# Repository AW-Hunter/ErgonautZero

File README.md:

# Ergonaut Zero

*Ergonaut Zero in Modern Case*

Ergonaut Zero is fork for an open-source ergonomic wireless split mechanical keyboard Ergonaut Zero designed by Ergonaut Keyboards.
It's based on RP2040 Zero MCU and use wire between split, unlike original.

## Features

* Low-profile, which will reduce strain on your beautiful hands;
* Split. You can put the keyboard where it'll be comfortable exactly for you;
* Wide availability and range of [compatible keycaps](https://ergonautkb.com/docs/switches/gateron-low-profile#keycaps-compatibility);
* Easily replaceable [switches](https://ergonautkb.com/docs/switches/gateron-low-profile#ks-33-v2) thanks to hot-swap sockets;
* Budget-friendly, because:
  * It uses relatively cheap and widely available RP2040 Zero as MCU;
  * It uses one PCB design for both halves of the keyboard;
  * Everything except PCB's, components and hardware (screws, nuts) can be 3D printed.
* Beginner-friendly, because:
  * PCB is easy to solder;
  * Cases are easy to print.
* Free in terms of hardware design. It's licensed under permissive [CERN-OHL-P v2](https://ohwr.org/cern_ohl_p_v2.pdf) license, which means:
  * you are free to manufacture it yourself;
  * you are free to sell your manufactured hardware for profit.

## Build Guide

In progress

## Firmware

Firmware can be found in this repository.

## Gerbers

REPLACE!!

| Front                                            | Back                                                 |
| ------------------------------------------------ | ---------------------------------------------------- |
|  |  |

* [Gerbers for JLCPCB](../../releases/latest/download/pcb-JLCPCB_gerbers.zip)
* [Gerbers for PCBWay](../../releases/latest/download/pcb-PCBWay_gerbers.zip)

## Contacts

* Documentation portal of original board: https://ergonautkb.com
* Telegram of original board: https://ergonautkb.t.me
* Telegram of original board (ru): https://ergonautkb_ru.t.me
*

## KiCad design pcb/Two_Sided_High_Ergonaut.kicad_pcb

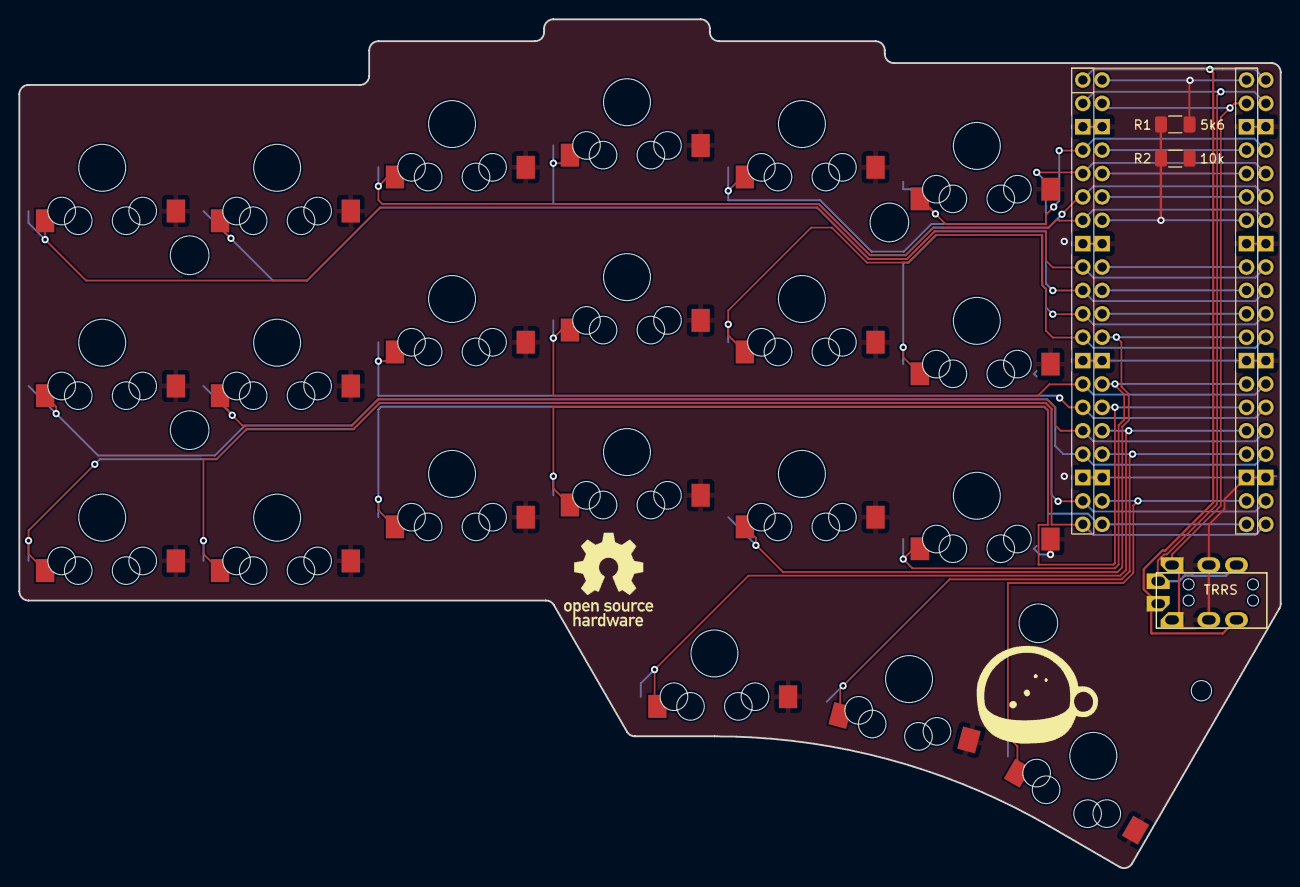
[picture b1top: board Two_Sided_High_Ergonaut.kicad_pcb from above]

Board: 2 copper layers, 137.0 x 92.2 mm, 30 parts (0 on the bottom side), 27 nets.

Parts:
H1, H2, H3, H4: MountingHole; Hole_4.2mm
H8: StandoffHole; Hole_2.2mm
J1: TRRS; MJ-4PP-9_Cantor_MX_TX-RX_Crossover
R1: 5k6; R_1206_3216Metric_Pad1.30x1.75mm_HandSolder
R2: 10k; R_1206_3216Metric_Pad1.30x1.75mm_HandSolder
SW1, SW2, SW3, SW4, SW5, SW6, SW7, SW8, SW9, SW10, SW11, SW12, SW13, SW14, SW15, SW16, SW17, SW18, SW19, SW20, SW21: SW_SPST; KS-27_KS-33_Hotswap_1U_DUAL
U2: Pico; RPi_Pico_SMD_TH

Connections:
GND: J1.3 (RING1), J1.4 (RING2), R2.2, SW1.2 (B), SW2.2 (B), SW3.2 (B), SW4.2 (B), SW5.2 (B), SW6.2 (B), SW7.2 (B), SW8.2 (B), SW9.2 (B), SW10.2 (B), SW11.2 (B), SW12.2 (B), SW13.2 (B), SW14.2 (B), SW15.2 (B), SW16.2 (B), SW17.2 (B), SW18.2 (B), SW19.2 (B), SW20.2 (B), SW21.2 (B), U2.3 (GND), U2.8 (GND), U2.13 (GND), U2.18 (GND), U2.23 (GND), U2.28 (GND), U2.33 (AGND), U2.38 (GND)
unnamed: SW1.1 (A), U2.9 (GPIO6)
unnamed: SW2.1 (A), U2.10 (GPIO7)
unnamed: SW3.1 (A), U2.7 (GPIO5)
unnamed: SW4.1 (A), U2.6 (GPIO4)
unnamed: SW5.1 (A), U2.5 (GPIO3)
unnamed: SW6.1 (A), U2.4 (GPIO2)
unnamed: SW7.1 (A), U2.17 (GPIO13)
unnamed: SW8.1 (A), U2.16 (GPIO12)
unnamed: SW9.1 (A), U2.15 (GPIO11)
unnamed: SW10.1 (A), U2.14 (GPIO10)
unnamed: SW11.1 (A), U2.12 (GPIO9)
unnamed: SW12.1 (A), U2.11 (GPIO8)
unnamed: SW13.1 (A), U2.19 (GPIO14)
unnamed: SW16.1 (A), U2.26 (GPIO20)
unnamed: SW15.1 (A), U2.21 (GPIO16)
unnamed: SW14.1 (A), U2.20 (GPIO15)
unnamed: SW17.1 (A), U2.29 (GPIO22)
unnamed: SW18.1 (A), U2.27 (GPIO21)
unnamed: SW19.1 (A), U2.25 (GPIO19)
unnamed: SW20.1 (A), U2.24 (GPIO18)
unnamed: SW21.1 (A), U2.22 (GPIO17)
RX: J1.1 (SLEEVE), J1.4 (RING2), U2.2 (GPIO1)
TX: J1.1 (SLEEVE), J1.3 (RING1), U2.1 (GPIO0)
VBUS: R1.1, U2.40 (VBUS)
VBUS_SENSE: R1.2, R2.1, U2.34 (GPIO28_ADC2)
VCC: J1.2 (TIP), U2.39 (VSYS)

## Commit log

2024-03-19 Add files via upload
    Added One-Pi Low and High version
